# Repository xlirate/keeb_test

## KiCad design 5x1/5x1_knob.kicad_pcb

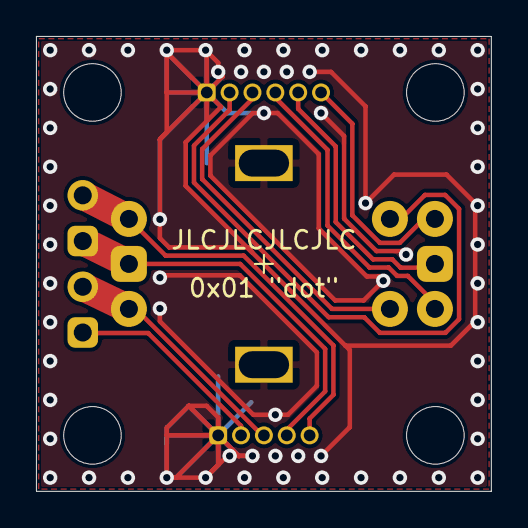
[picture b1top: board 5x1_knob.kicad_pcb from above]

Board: 2 copper layers, 25.3 x 25.3 mm, 4 parts (0 on the bottom side), 10 nets.

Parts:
J_1: Conn_01x06_Male; PinHeader_1x06_P1.27mm_Vertical
J_2: Conn_01x05_Male; PinHeader_1x05_P1.27mm_Vertical
SW_1: Double_rotary_Encoder_Switch; double_encoder
SW_2: analog_encoder; PinHeader_1x04_P2.54mm_Vertical

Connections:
K_GND: J_1.1, J_2.1
unnamed: J_1.2, SW_1.S2
unnamed: J_1.3, SW_1.S1
unnamed: J_1.4, SW_1.b
unnamed: J_1.5, SW_1.c
unnamed: J_1.6, SW_1.a
unnamed: J_2.2, SW_2.4
unnamed: J_2.3, SW_1.B, SW_2.3
unnamed: J_2.4, SW_1.C, SW_2.2
unnamed: J_2.5, SW_1.A, SW_2.1

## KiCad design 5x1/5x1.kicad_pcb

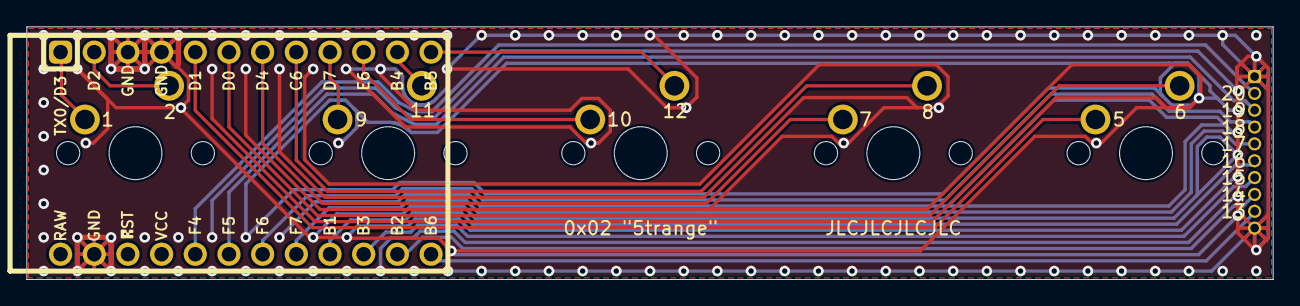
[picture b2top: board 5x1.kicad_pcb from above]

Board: 2 copper layers, 94.0 x 19.1 mm, 7 parts (1 on the bottom side), 19 nets.

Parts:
J_0: Conn_01x10_Male; PinHeader_1x10_P1.27mm_Vertical
MX_1, MX_2, MX_3, MX_4, MX_5: MX-NoLED; MXOnly-1U-NoLED
U1: Elite-C; ArduinoProMicro

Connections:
C0: MX_1.1, U1.1
C1: MX_2.1, U1.9
C2: MX_3.1, U1.10
C3: MX_4.1, U1.7
C4: MX_5.1, U1.5
GND: J_0.1, J_0.10, U1.3, U1.4, U1.23
unnamed: J_0.2, U1.20
unnamed: J_0.3, U1.19
unnamed: J_0.4, U1.18
unnamed: J_0.5, U1.17
unnamed: J_0.6, U1.16
unnamed: J_0.7, U1.15
unnamed: J_0.8, U1.14
unnamed: J_0.9, U1.13
R0: MX_1.2, U1.2
R1: MX_2.2, U1.11
R2: MX_3.2, U1.12
R3: MX_4.2, U1.8
R4: MX_5.2, U1.6

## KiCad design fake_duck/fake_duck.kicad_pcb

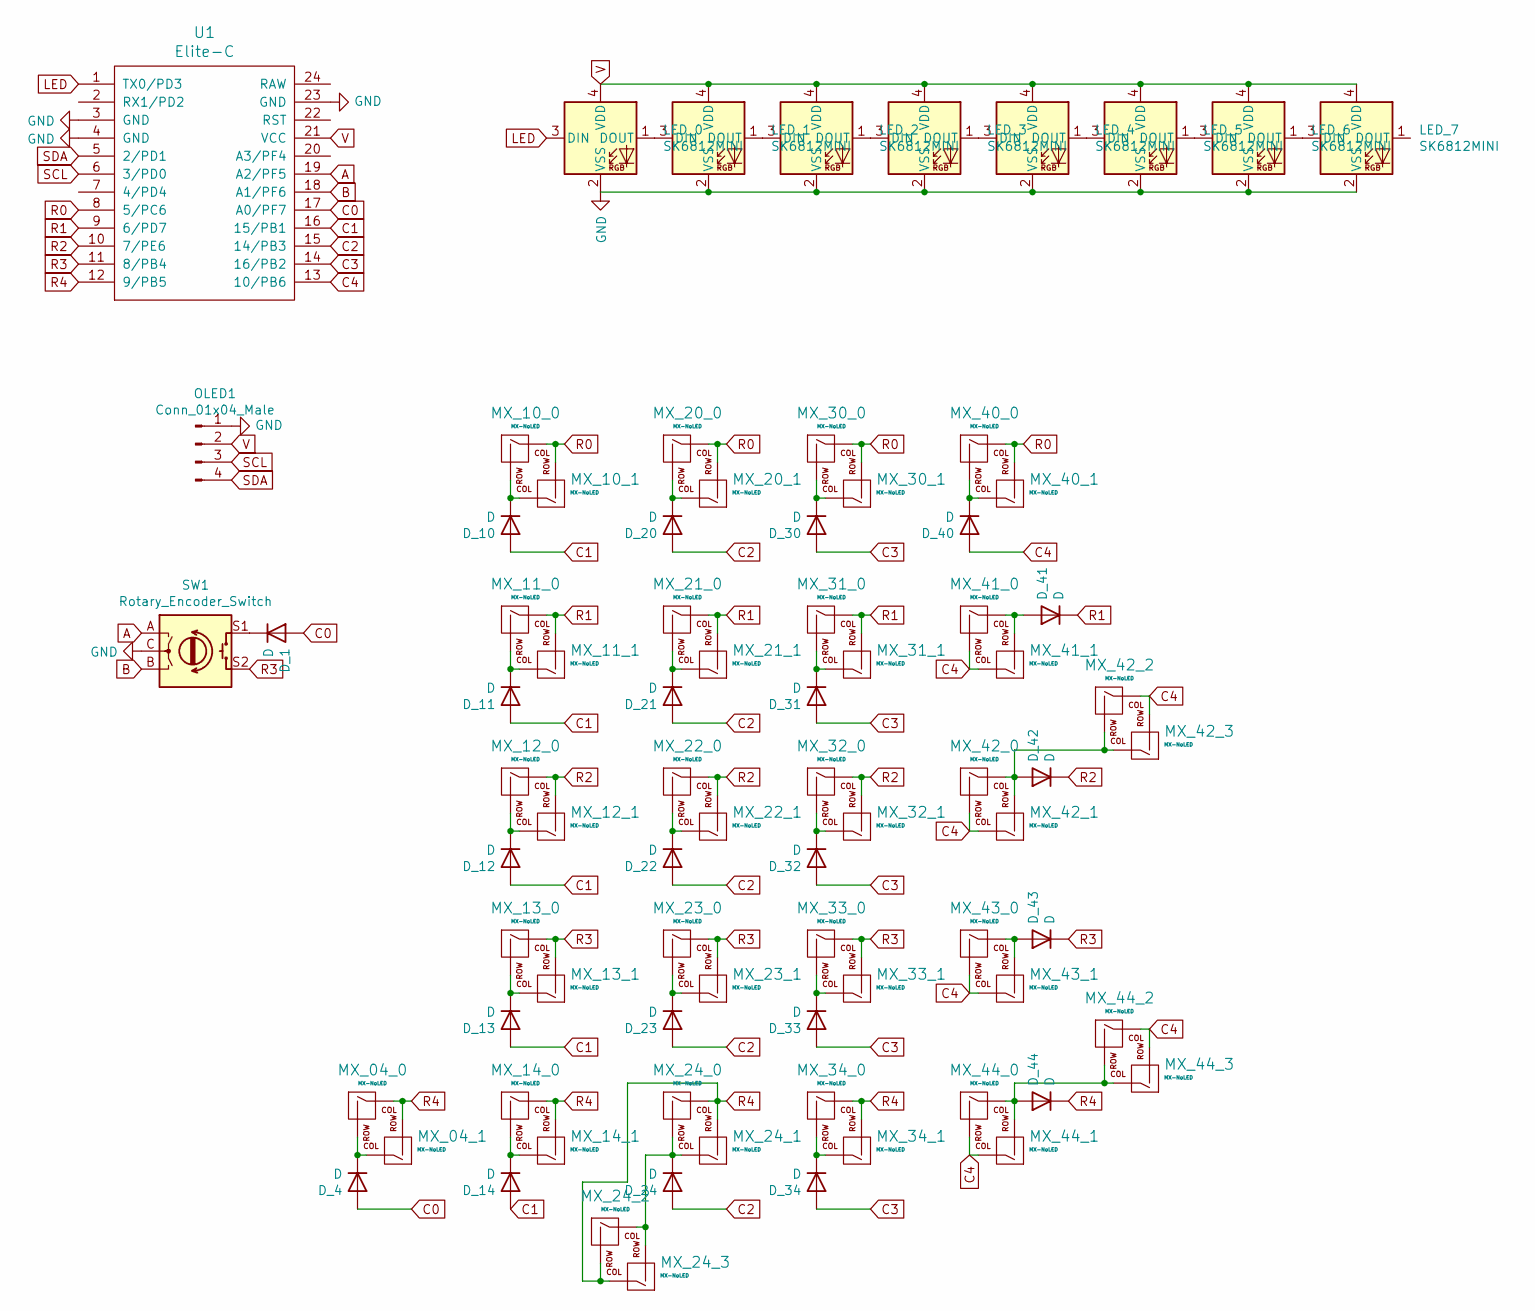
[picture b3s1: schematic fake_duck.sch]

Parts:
D_1, D_4, D_10, D_11, D_12, D_13, D_14, D_20, D_21, D_22, D_23, D_24, D_30, D_31, D_32, D_33, D_34, D_40, D_41, D_42, D_43, D_44: D; Diode_Long
LED_0, LED_1, LED_2, LED_3, LED_4, LED_5, LED_6, LED_7: SK6812MINI; LED_SK6812MINI_PLCC4_3.5x3.5mm_P1.75mm
MX_04_0, MX_10_0, MX_11_0, MX_12_0, MX_13_0, MX_14_0, MX_20_0, MX_21_0, MX_22_0, MX_23_0, MX_24_0, MX_30_0, MX_31_0, MX_32_0, MX_33_0, MX_34_0, MX_40_0, MX_41_0, MX_42_0, MX_43_0, MX_44_0: MX-NoLED; MXOnly-1U-NoLED
MX_04_1, MX_10_1, MX_11_1, MX_12_1, MX_13_1, MX_14_1, MX_20_1, MX_21_1, MX_22_1, MX_23_1, MX_24_1, MX_24_3, MX_30_1, MX_31_1, MX_32_1, MX_33_1, MX_34_1, MX_40_1, MX_41_1, MX_42_1, MX_42_3, MX_43_1, MX_44_1, MX_44_3: MX-NoLED; MXOnly-1U-Hotswap
MX_24_2, MX_42_2, MX_44_2: MX-NoLED; MXOnly-2U-NoLED
OLED1: Conn_01x04_Male; PinHeader_1x04_P2.54mm_Vertical
SW1: Rotary_Encoder_Switch; RotaryEncoder_Alps_EC11E-Switch_Vertical_H20mm
U1: Elite-C; ArduinoProMicro

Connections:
A: SW1.A, U1.19 (A2/PF5)
B: SW1.B, U1.18 (A1/PF6)
C0: D_1.2 (A), D_4.2 (A), U1.17 (A0/PF7)
C1: D_10.2 (A), D_11.2 (A), D_12.2 (A), D_13.2 (A), D_14.2 (A), U1.16 (15/PB1)
C2: D_20.2 (A), D_21.2 (A), D_22.2 (A), D_23.2 (A), D_24.2 (A), U1.15 (14/PB3)
C3: D_30.2 (A), D_31.2 (A), D_32.2 (A), D_33.2 (A), D_34.2 (A), U1.14 (16/PB2)
C4: D_40.2 (A), MX_41_0.2 (ROW), MX_41_1.1 (COL), MX_42_0.2 (ROW), MX_42_1.1 (COL), MX_42_2.1 (COL), MX_42_3.2 (ROW), MX_43_0.2 (ROW), MX_43_1.1 (COL), MX_44_0.2 (ROW), MX_44_1.1 (COL), MX_44_2.1 (COL), MX_44_3.2 (ROW), U1.13 (10/PB6)
GND: LED_0.2 (VSS), LED_1.2 (VSS), LED_2.2 (VSS), LED_3.2 (VSS), LED_4.2 (VSS), LED_5.2 (VSS), LED_6.2 (VSS), LED_7.2 (VSS), OLED1.1, SW1.C, U1.3 (GND), U1.4 (GND), U1.23 (GND)
LED: LED_0.3 (DIN), U1.1 (TX0/PD3)
unnamed: D_1.1 (K), SW1.S1
unnamed: D_4.1 (K), MX_04_0.2 (ROW), MX_04_1.1 (COL)
unnamed: D_10.1 (K), MX_10_0.2 (ROW), MX_10_1.1 (COL)
unnamed: D_11.1 (K), MX_11_0.2 (ROW), MX_11_1.1 (COL)
unnamed: D_12.1 (K), MX_12_0.2 (ROW), MX_12_1.1 (COL)
unnamed: D_13.1 (K), MX_13_0.2 (ROW), MX_13_1.1 (COL)
unnamed: D_14.1 (K), MX_14_0.2 (ROW), MX_14_1.1 (COL)
unnamed: D_20.1 (K), MX_20_0.2 (ROW), MX_20_1.1 (COL)
unnamed: D_21.1 (K), MX_21_0.2 (ROW), MX_21_1.1 (COL)
unnamed: D_22.1 (K), MX_22_0.2 (ROW), MX_22_1.1 (COL)
unnamed: D_23.1 (K), MX_23_0.2 (ROW), MX_23_1.1 (COL)
unnamed: D_24.1 (K), MX_24_0.2 (ROW), MX_24_1.1 (COL), MX_24_2.1 (COL), MX_24_3.2 (ROW)
unnamed: D_30.1 (K), MX_30_0.2 (ROW), MX_30_1.1 (COL)
unnamed: D_31.1 (K), MX_31_0.2 (ROW), MX_31_1.1 (COL)
unnamed: D_32.1 (K), MX_32_0.2 (ROW), MX_32_1.1 (COL)
unnamed: D_33.1 (K), MX_33_0.2 (ROW), MX_33_1.1 (COL)
unnamed: D_34.1 (K), MX_34_0.2 (ROW), MX_34_1.1 (COL)
unnamed: D_40.1 (K), MX_40_0.2 (ROW), MX_40_1.1 (COL)
unnamed: D_41.2 (A), MX_41_0.1 (COL), MX_41_1.2 (ROW)
unnamed: D_42.2 (A), MX_42_0.1 (COL), MX_42_1.2 (ROW), MX_42_2.2 (ROW), MX_42_3.1 (COL)
unnamed: D_43.2 (A), MX_43_0.1 (COL), MX_43_1.2 (ROW)
unnamed: D_44.2 (A), MX_44_0.1 (COL), MX_44_1.2 (ROW), MX_44_2.2 (ROW), MX_44_3.1 (COL)
unnamed: LED_0.1 (DOUT), LED_1.3 (DIN)
unnamed: LED_1.1 (DOUT), LED_2.3 (DIN)
unnamed: LED_2.1 (DOUT), LED_3.3 (DIN)
unnamed: LED_3.1 (DOUT), LED_4.3 (DIN)
unnamed: LED_4.1 (DOUT), LED_5.3 (DIN)
unnamed: LED_5.1 (DOUT), LED_6.3 (DIN)
unnamed: LED_6.1 (DOUT), LED_7.3 (DIN)
R0: MX_10_0.1 (COL), MX_10_1.2 (ROW), MX_20_0.1 (COL), MX_20_1.2 (ROW), MX_30_0.1 (COL), MX_30_1.2 (ROW), MX_40_0.1 (COL), MX_40_1.2 (ROW), U1.8 (5/PC6)
R1: D_41.1 (K), MX_11_0.1 (COL), MX_11_1.2 (ROW), MX_21_0.1 (COL), MX_21_1.2 (ROW), MX_31_0.1 (COL), MX_31_1.2 (ROW), U1.9 (6/PD7)
R2: D_42.1 (K), MX_12_0.1 (COL), MX_12_1.2 (ROW), MX_22_0.1 (COL), MX_22_1.2 (ROW), MX_32_0.1 (COL), MX_32_1.2 (ROW), U1.10 (7/PE6)
R3: D_43.1 (K), MX_13_0.1 (COL), MX_13_1.2 (ROW), MX_23_0.1 (COL), MX_23_1.2 (ROW), MX_33_0.1 (COL), MX_33_1.2 (ROW), SW1.S2, U1.11 (8/PB4)
R4: D_44.1 (K), MX_04_0.1 (COL), MX_04_1.2 (ROW), MX_14_0.1 (COL), MX_14_1.2 (ROW), MX_24_0.1 (COL), MX_24_1.2 (ROW), MX_24_2.2 (ROW), MX_24_3.1 (COL), MX_34_0.1 (COL), MX_34_1.2 (ROW), U1.12 (9/PB5)
SCL: OLED1.3, U1.6 (3/PD0)
SDA: OLED1.4, U1.5 (2/PD1)
V: LED_0.4 (VDD), LED_1.4 (VDD), LED_2.4 (VDD), LED_3.4 (VDD), LED_4.4 (VDD), LED_5.4 (VDD), LED_6.4 (VDD), LED_7.4 (VDD), OLED1.2, U1.21 (VCC)

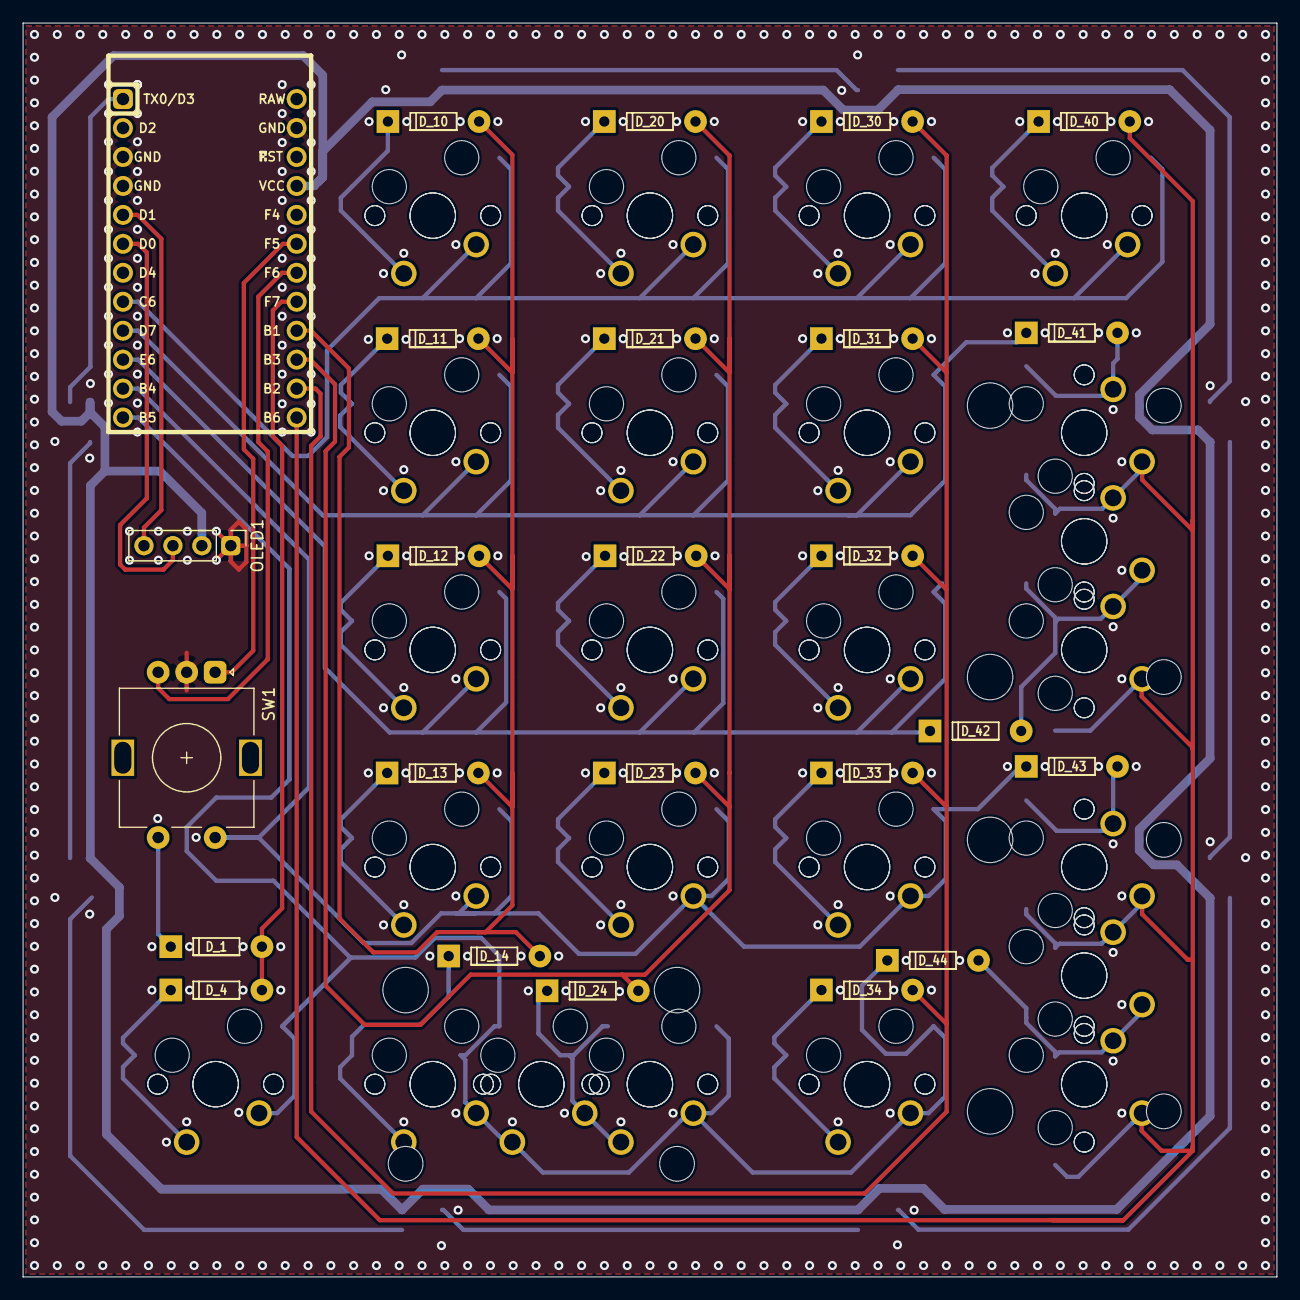
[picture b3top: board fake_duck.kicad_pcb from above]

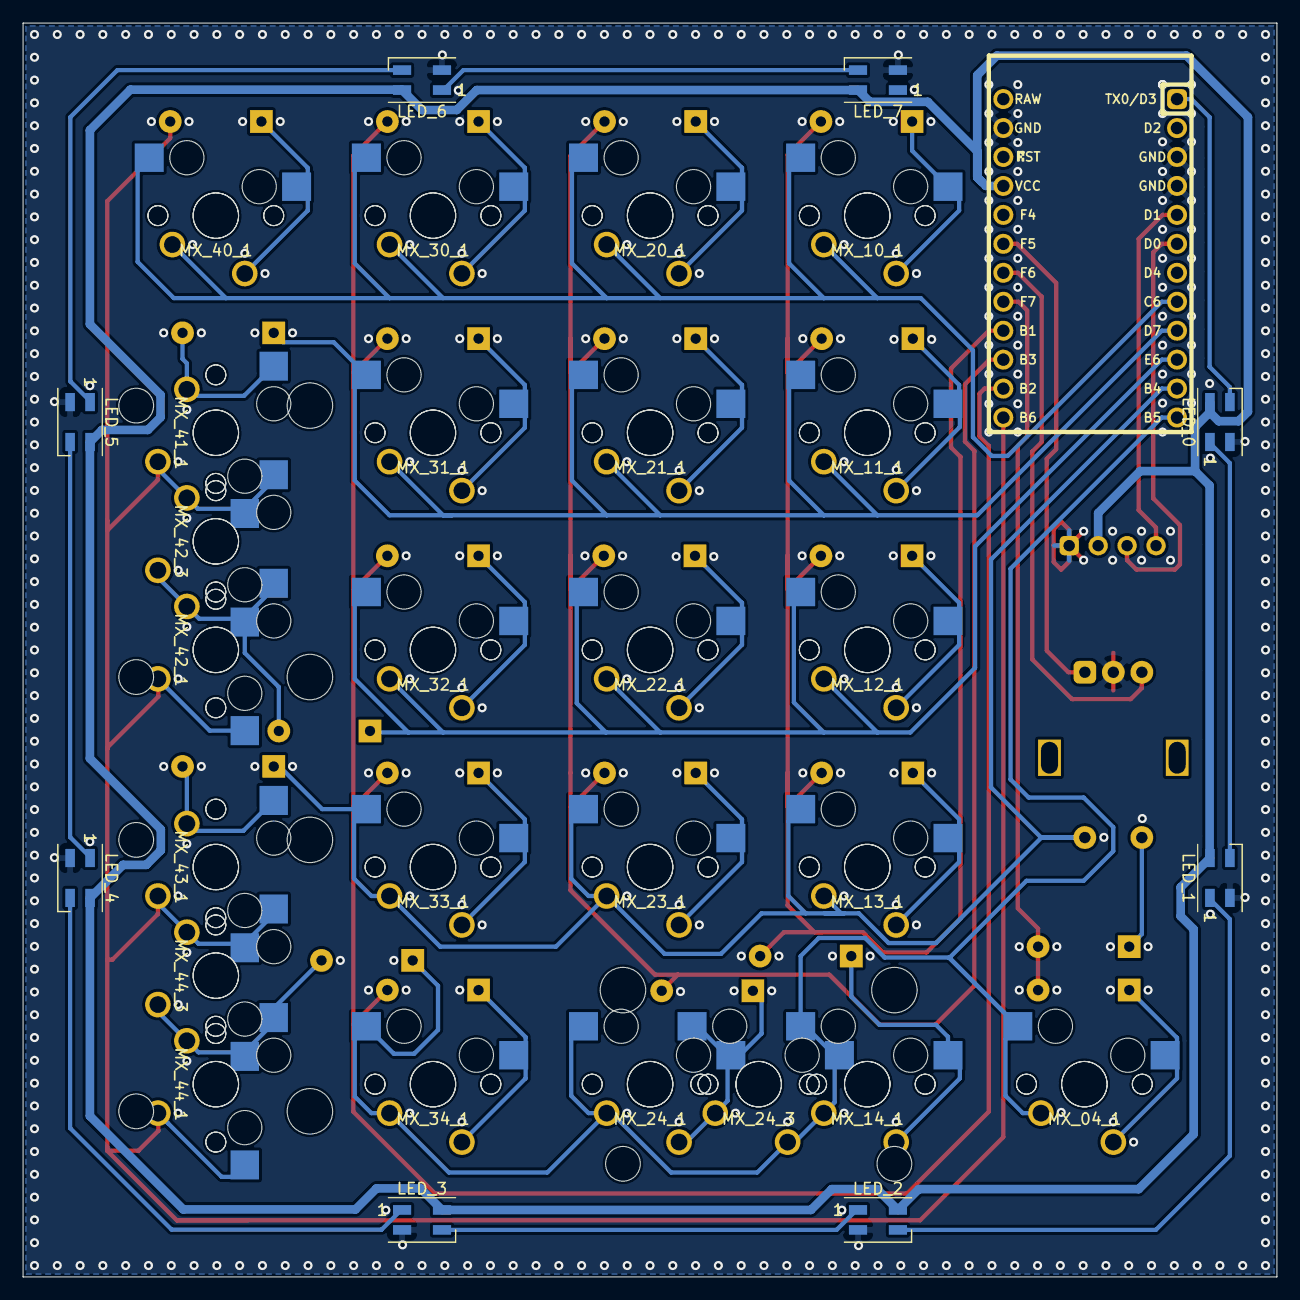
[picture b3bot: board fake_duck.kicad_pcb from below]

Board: 2 copper layers, 110.0 x 110.0 mm, 81 parts (8 on the bottom side), 46 nets.

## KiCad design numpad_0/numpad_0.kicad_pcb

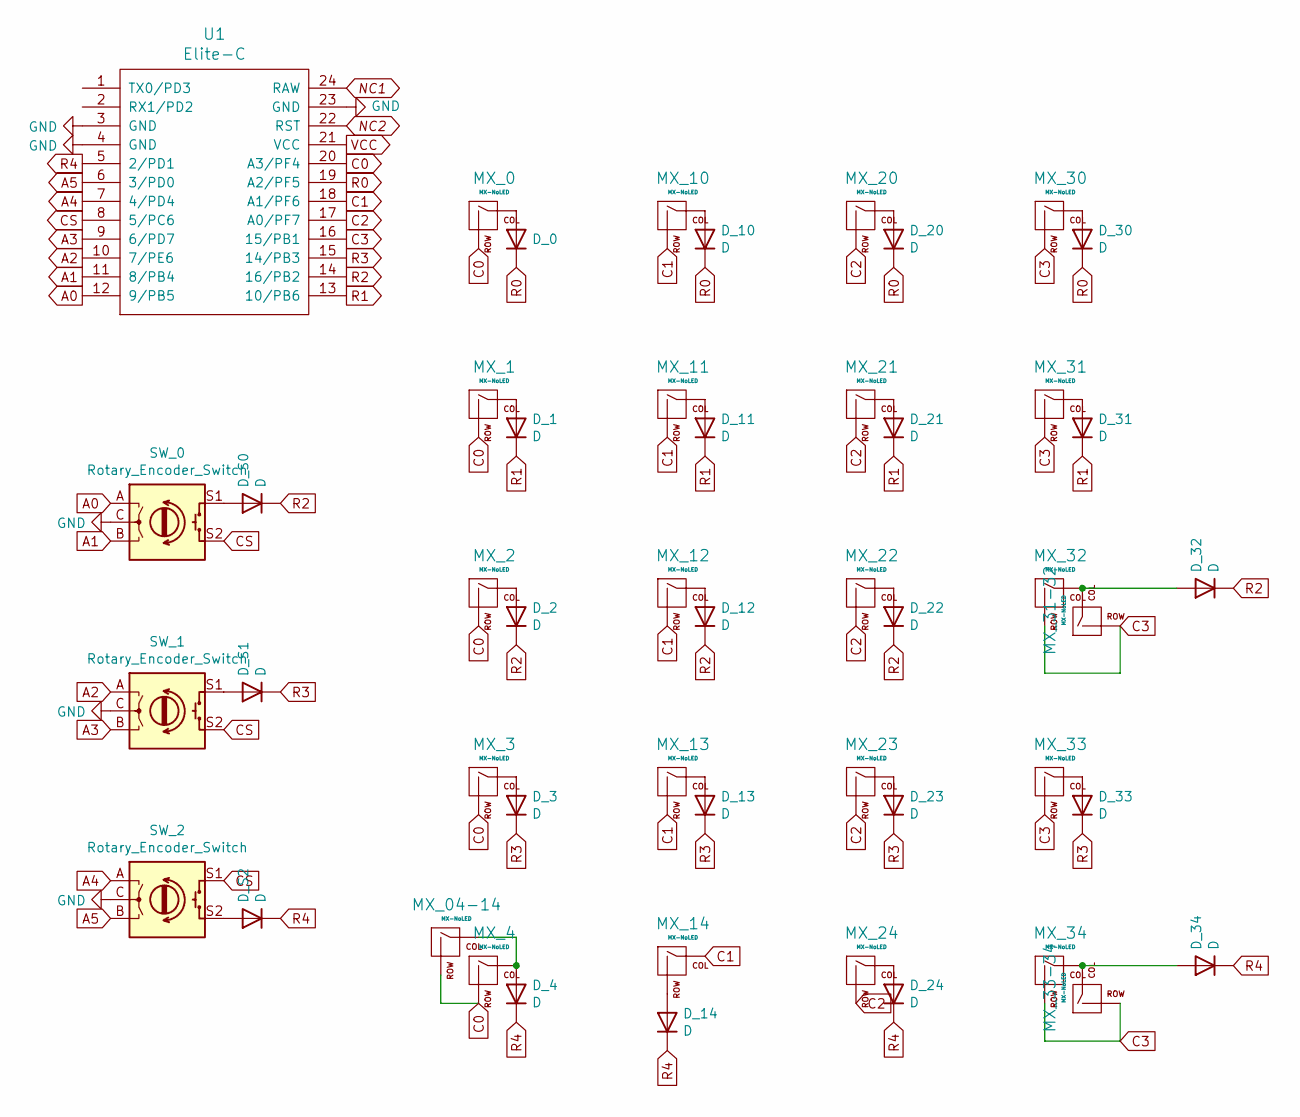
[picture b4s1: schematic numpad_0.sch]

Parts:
D_0, D_1, D_2, D_3, D_4, D_10, D_11, D_12, D_13, D_14, D_20, D_21, D_22, D_23, D_24, D_30, D_31, D_32, D_33, D_34: D; Diode-dual
D_S0, D_S1, D_S2: D; Diode-dual
MX_0, MX_1, MX_2, MX_3, MX_4, MX_10, MX_11, MX_12, MX_13, MX_14, MX_20, MX_21, MX_22, MX_23, MX_24, MX_30, MX_31, MX_32, MX_33, MX_34: MX-NoLED; MXOnly-1U-NoLED
MX_04-14, MX_31-32, MX_33-34: MX-NoLED; MXOnly-2U-NoLED
SW_0, SW_1, SW_2: Rotary_Encoder_Switch; RotaryEncoder_Alps_EC11E-Switch_Vertical_H20mm
U1: Elite-C; ArduinoProMicro

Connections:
A0: SW_0.A, U1.12 (9/PB5)
A1: SW_0.B, U1.11 (8/PB4)
A2: SW_1.A, U1.10 (7/PE6)
A3: SW_1.B, U1.9 (6/PD7)
A4: SW_2.A, U1.7 (4/PD4)
A5: SW_2.B, U1.6 (3/PD0)
C0: MX_0.2 (ROW), MX_1.2 (ROW), MX_2.2 (ROW), MX_3.2 (ROW), MX_4.2 (ROW), MX_04-14.2 (ROW), U1.20 (A3/PF4)
C1: MX_10.2 (ROW), MX_11.2 (ROW), MX_12.2 (ROW), MX_13.2 (ROW), MX_14.1 (COL), U1.18 (A1/PF6)
C2: MX_20.2 (ROW), MX_21.2 (ROW), MX_22.2 (ROW), MX_23.2 (ROW), MX_24.2 (ROW), U1.17 (A0/PF7)
C3: MX_30.2 (ROW), MX_31.2 (ROW), MX_31-32.2 (ROW), MX_32.2 (ROW), MX_33.2 (ROW), MX_33-34.2 (ROW), MX_34.2 (ROW), U1.16 (15/PB1)
CS: SW_0.S2, SW_1.S2, SW_2.S1, U1.8 (5/PC6)
GND: SW_0.C, SW_1.C, SW_2.C, U1.3 (GND), U1.4 (GND), U1.23 (GND)
NC1: U1.24 (RAW)
NC2: U1.22 (RST)
unnamed: D_0.2 (A), MX_0.1 (COL)
unnamed: D_1.2 (A), MX_1.1 (COL)
unnamed: D_2.2 (A), MX_2.1 (COL)
unnamed: D_3.2 (A), MX_3.1 (COL)
unnamed: D_4.2 (A), MX_4.1 (COL), MX_04-14.1 (COL)
unnamed: D_10.2 (A), MX_10.1 (COL)
unnamed: D_11.2 (A), MX_11.1 (COL)
unnamed: D_12.2 (A), MX_12.1 (COL)
unnamed: D_13.2 (A), MX_13.1 (COL)
unnamed: D_14.2 (A), MX_14.2 (ROW)
unnamed: D_20.2 (A), MX_20.1 (COL)
unnamed: D_21.2 (A), MX_21.1 (COL)
unnamed: D_22.2 (A), MX_22.1 (COL)
unnamed: D_23.2 (A), MX_23.1 (COL)
unnamed: D_24.2 (A), MX_24.1 (COL)
unnamed: D_30.2 (A), MX_30.1 (COL)
unnamed: D_31.2 (A), MX_31.1 (COL)
unnamed: D_32.2 (A), MX_31-32.1 (COL), MX_32.1 (COL)
unnamed: D_33.2 (A), MX_33.1 (COL)
unnamed: D_34.2 (A), MX_33-34.1 (COL), MX_34.1 (COL)
unnamed: D_S0.2 (A), SW_0.S1
unnamed: D_S1.2 (A), SW_1.S1
unnamed: D_S2.2 (A), SW_2.S2
R0: D_0.1 (K), D_10.1 (K), D_20.1 (K), D_30.1 (K), U1.19 (A2/PF5)
R1: D_1.1 (K), D_11.1 (K), D_21.1 (K), D_31.1 (K), U1.13 (10/PB6)
R2: D_2.1 (K), D_12.1 (K), D_22.1 (K), D_32.1 (K), D_S0.1 (K), U1.14 (16/PB2)
R3: D_3.1 (K), D_13.1 (K), D_23.1 (K), D_33.1 (K), D_S1.1 (K), U1.15 (14/PB3)
R4: D_4.1 (K), D_14.1 (K), D_24.1 (K), D_34.1 (K), D_S2.1 (K), U1.5 (2/PD1)
VCC: U1.21 (VCC)

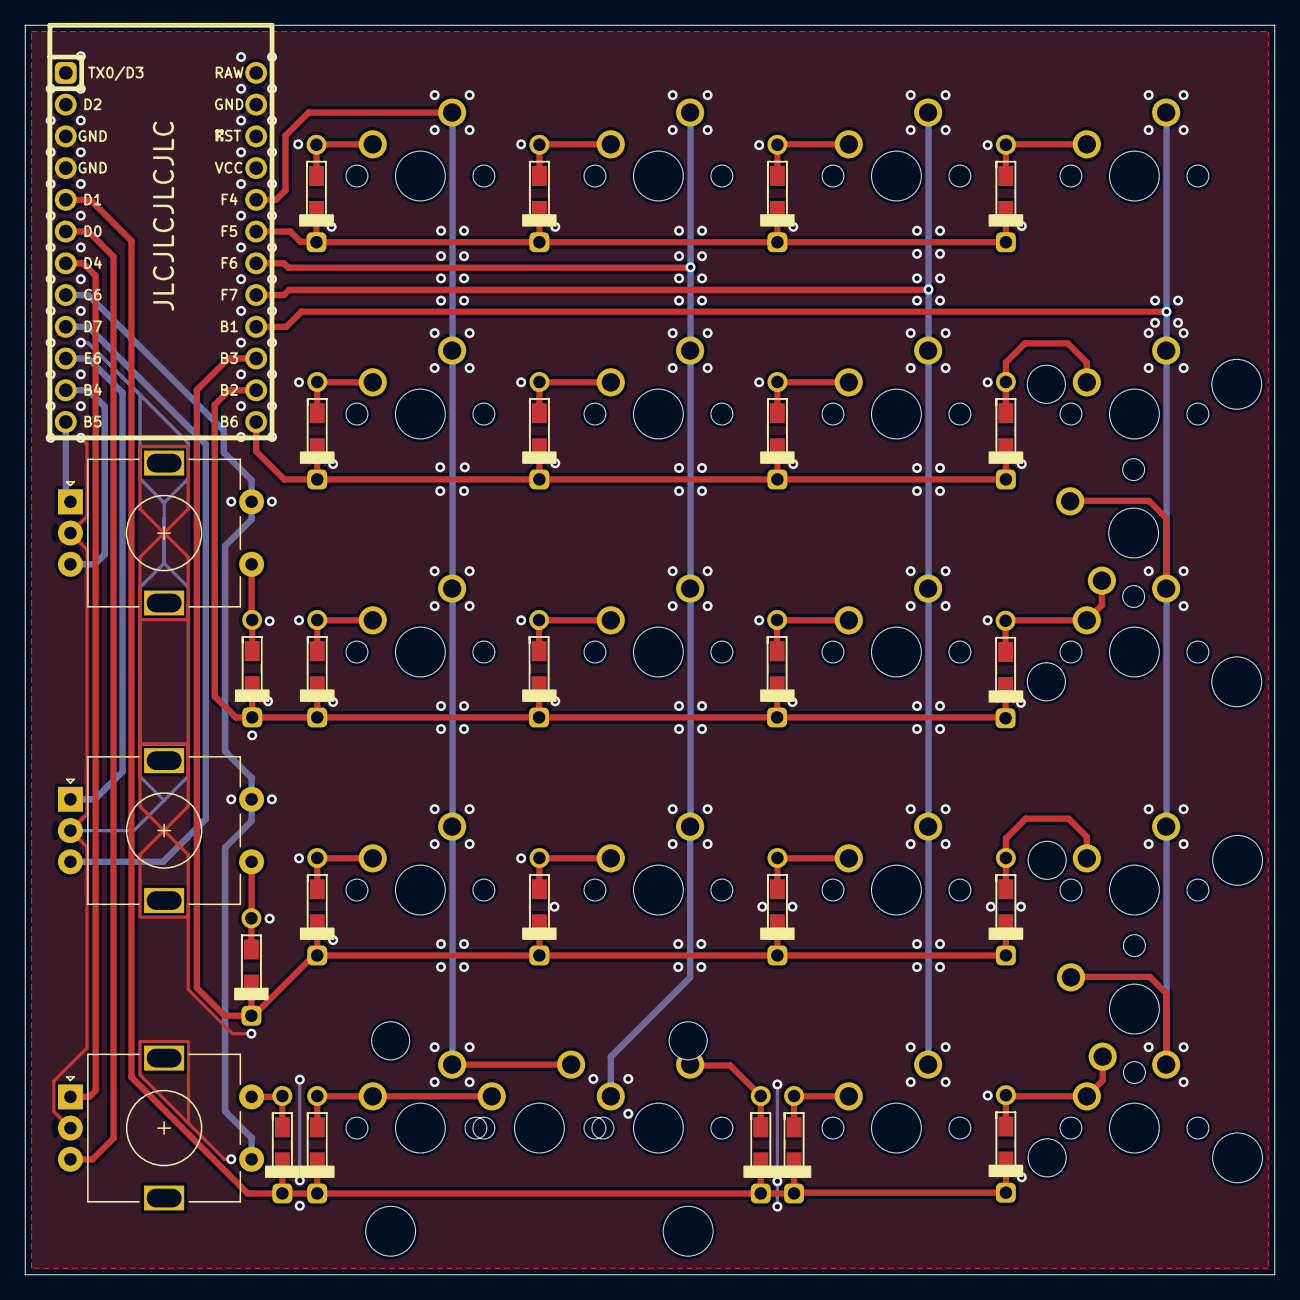
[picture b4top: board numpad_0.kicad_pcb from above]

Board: 2 copper layers, 100.0 x 100.0 mm, 50 parts (0 on the bottom side), 40 nets.

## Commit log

2021-05-02 created blank project
2021-05-02 libs added
2021-05-17 made basic 3 knob 4x5 pad
2021-05-18 V0, sent for printing
2021-05-25 5x1 commission 'done'
2021-05-25 added silkscreen
2021-06-06 5trange dot as built
2021-06-09 added but have not routed the fake duck
2021-06-09 grounding worked out on the fake duck
2021-06-18 touched up things and detached the case ground and electrical ground on the dot board
